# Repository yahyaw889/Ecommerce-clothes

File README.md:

<p align="center"></p>

<p align="center">

</p>

## About Laravel

Laravel is a web application framework with expressive, elegant syntax. We believe development must be an enjoyable and creative experience to be truly fulfilling. Laravel takes the pain out of development by easing common tasks used in many web projects, such as:

- [Simple, fast routing engine](https://laravel.com/docs/routing).
- [Powerful dependency injection container](https://laravel.com/docs/container).
- Multiple back-ends for [session](https://laravel.com/docs/session) and [cache](https://laravel.com/docs/cache) storage.
- Expressive, intuitive [database ORM](https://laravel.com/docs/eloquent).
- Database agnostic [schema migrations](https://laravel.com/docs/migrations).
- [Robust background job processing](https://laravel.com/docs/queues).
- [Real-time event broadcasting](https://laravel.com/docs/broadcasting).

Laravel is accessible, powerful, and provides tools required for large, robust applications.

## Learning Laravel

Laravel has the most extensive and thorough [documentation](https://laravel.com/docs) and video tutorial library of all modern web application frameworks, making it a breeze to get started with the framework.

You may also try the [Laravel Bootcamp](https://bootcamp.laravel.com), where you will be guided through building a modern Laravel application from scratch.

If you don't feel like reading, [Laracasts](https://laracasts.com) can help. Laracasts contains thousands of video tutorials on a range of topics including Laravel, modern PHP, unit testing, and JavaScript. Boost your skills by digging into our comprehensive video library.

## Laravel Sponsors

We would like to extend our thanks to the following sponsors for funding Laravel development. If you are interested in becoming a sponsor, please visit the [Laravel Partners program](https://partners.laravel.com).

### Premium Partners

- **[Vehikl](https://vehikl.com/)**
- **[Tighten Co.](https://tighten.co)**
- **[WebReinvent](https://webreinvent.com/)**
- **[Kirschbaum Development Group](https://kirschbaumdevelopment.com)**
- **[64 Robots](https://64robots.com)**
- **[Curotec](https://www.curotec.com/services/technologies/laravel/)**
- **[Cyber-Duck](https://cyber-duck.co.uk)**
- **[DevSquad](https://devsquad.com/hire-laravel-developers)**
- **[Jump24](https://jump24.co.uk)**
- **[Redberry](https://redberry.international/laravel/)**
- **[Active Logic](https://activelogic.com)**
- **[byte5](https://byte5.de)**
- **[OP.GG](https://op.gg)**

## Contributing

Thank you for considering contributing to the Laravel framework! The contribution guide can be found in the [Laravel documentation](https://laravel.com/docs/contributions).

## Code of Conduct

In order to ensure that the Laravel community is welcoming to all, please review and abide by the [Code of Conduct](https://laravel.com/docs/contributions#code-of-conduct).

## Security Vulnerabilities

If you discover a security vulnerability within Laravel, please send an e-mail to Taylor Otwell via [taylor@laravel.com](mailto:taylor@laravel.com). All security vulnerabilities will be promptly addressed.

## License

The Laravel framework is open-sourced software licensed under the [MIT license](https://opensource.org/licenses/MIT).
# E-ecommerce
# E-ecommerce

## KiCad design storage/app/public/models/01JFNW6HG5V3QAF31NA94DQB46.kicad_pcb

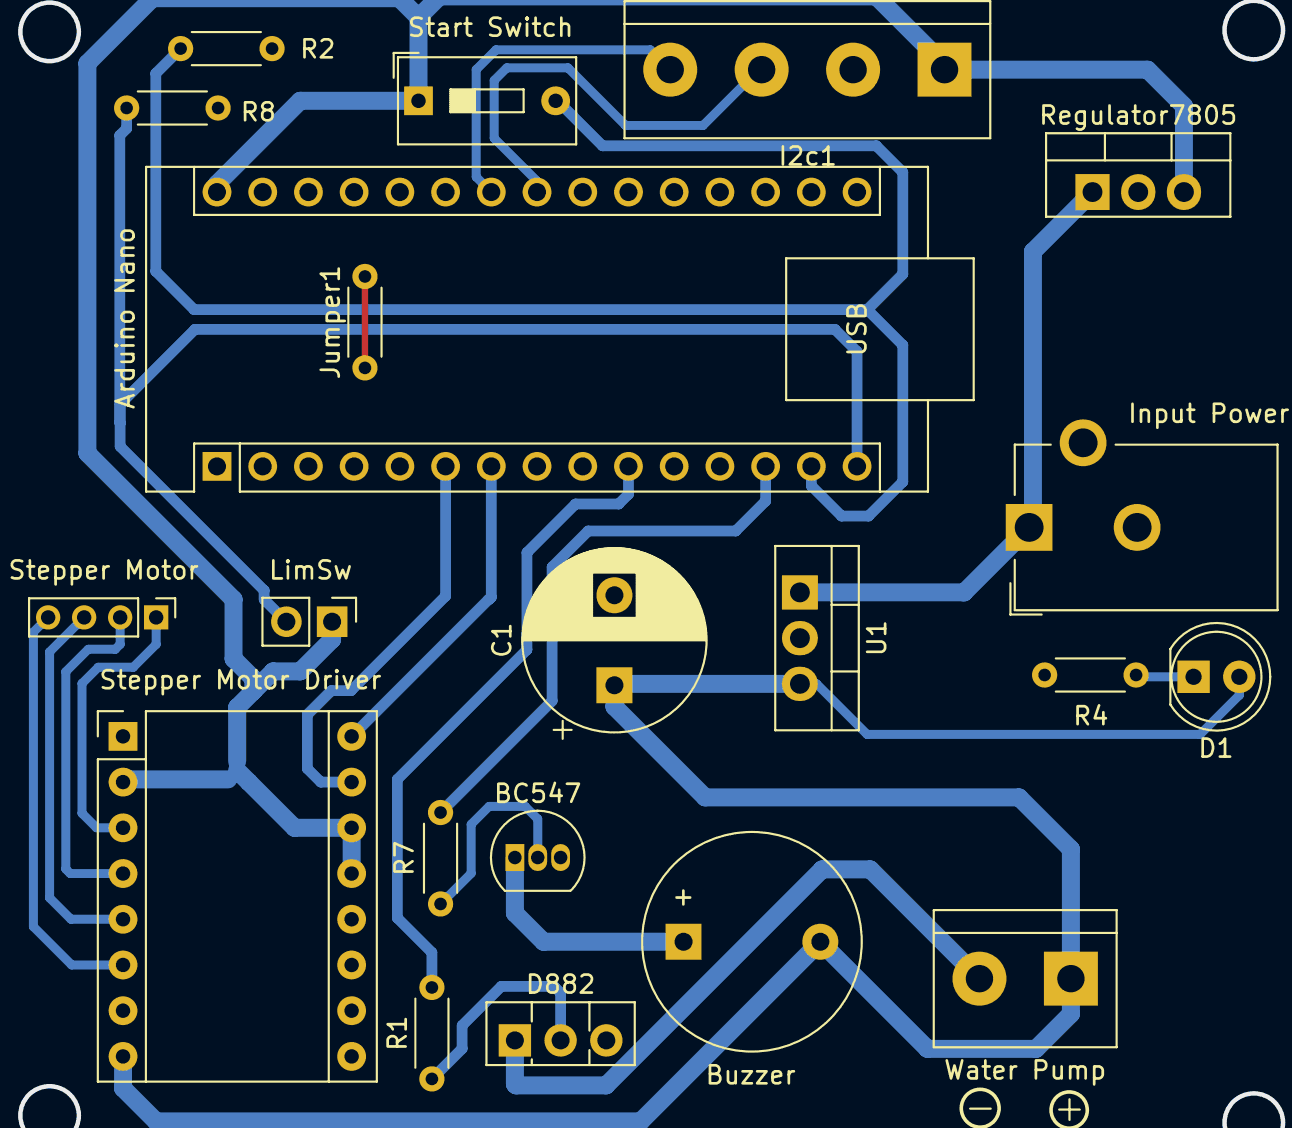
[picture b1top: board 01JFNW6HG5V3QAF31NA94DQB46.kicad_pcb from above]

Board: 2 copper layers, 21 parts (0 on the bottom side), 21 nets.

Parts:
Arduino Nano: Arduino_Nano_Every; Arduino_Nano
BC547: BC547; TO-92_Inline
Buzzer: Buzzer; Buzzer_12x9.5RM7.6
C1: 100u; CP_Radial_D10.0mm_P5.00mm
D1: LED; LED_D5.0mm
D882: BC547; TO-126-3_Vertical
I2c1: Screw_Terminal_01x04; TerminalBlock_bornier-4_P5.08mm
Input Power: Barrel_Jack_Switch; BarrelJack_CUI_PJ-102AH_Horizontal
Jumper1: R; R_Axial_DIN0204_L3.6mm_D1.6mm_P5.08mm_Horizontal
LimSw: Screw_Terminal_01x02; PinHeader_1x02_P2.54mm_Vertical
R1, R4, R7: 1k; R_Axial_DIN0204_L3.6mm_D1.6mm_P5.08mm_Horizontal
R2, R8: 10k; R_Axial_DIN0204_L3.6mm_D1.6mm_P5.08mm_Horizontal
Regulator7805: LM7805_TO220; TO-220-3_Vertical
Start Switch: SW_DPST_x2; SW_DIP_SPSTx01_Slide_9.78x4.72mm_W7.62mm_P2.54mm
Stepper Motor: Screw_Terminal_01x04; PinHeader_1x04_P2.00mm_Vertical
Stepper Motor Driver: Pololu_Breakout_A4988; Pololu_Breakout-16_15.2x20.3mm
U1: LM7812_TO220; TO-220-3_Vertical
Water Pump: Screw_Terminal_01x02; TerminalBlock_bornier-2_P5.08mm

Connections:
+5V: Arduino Nano.30 (VIN), I2c1.1, LimSw.1, Regulator7805.3 (VO), Start Switch.1 (A), Stepper Motor Driver.2 (VDD), Stepper Motor Driver.13 (~RESET), Stepper Motor Driver.14 (~SLEEP)
+12V: Buzzer.2 (+), C1.1, D1.2 (A), Stepper Motor Driver.8 (VMOT), U1.3 (VO), Water Pump.1
D3: Arduino Nano.6 (D3), Stepper Motor Driver.15 (STEP)
D4: Arduino Nano.7 (D4), Stepper Motor Driver.16 (DIR)
D8: Arduino Nano.10 (D7), R1.2
D10: Arduino Nano.13 (D10), R7.1
GND: Arduino Nano.4 (GND), Arduino Nano.29 (GND), BC547.3 (E), C1.2, D882.3 (E), I2c1.2, Input Power.2, Jumper1.1, Jumper1.2, R2.2, R4.1, R8.2, Regulator7805.2 (GND), Stepper Motor Driver.1 (GND), Stepper Motor Driver.7 (GND), U1.2 (GND)
unnamed: BC547.2 (B), R7.2
unnamed: BC547.1 (C), Buzzer.1 (-)
unnamed: D1.1 (K), R4.2
unnamed: D882.2 (B), R1.1
unnamed: D882.1 (C), Water Pump.2
unnamed: Arduino Nano.15 (MISO), LimSw.2, R8.1
unnamed: Arduino Nano.14 (MOSI), R2.1, Start Switch.2 (B)
unnamed: Stepper Motor.1, Stepper Motor Driver.3 (1B)
unnamed: Stepper Motor.2, Stepper Motor Driver.4 (1A)
unnamed: Stepper Motor.3, Stepper Motor Driver.5 (2A)
unnamed: Stepper Motor.4, Stepper Motor Driver.6 (2B)
SCL: Arduino Nano.24 (SCL/A5), I2c1.4
SDA: Arduino Nano.23 (SDA/A4), I2c1.3
Vin: Input Power.1, Regulator7805.1 (VI), U1.1 (VI)

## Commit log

2024-12-15 update on image show image
2024-12-15 Model add in the actions delete and view
2024-12-15 update on status catagery and brand isset acctive or Not acctive
2024-12-15 final project
2024-12-16 final ebrahim
2024-12-19 final v1
2024-12-21 v1.1
2024-12-21 small edit
2024-12-22 update notifaction
2025-01-02 add user api
2025-01-03 update models image to full path
2025-01-07 edit views
2025-01-09 edit socail image
2025-01-12 close limit of images in products
2025-01-14 enable delete image file
2025-01-14 add city
2025-01-15 edit city in order
2025-01-15 commit limition in order
2025-01-15 edit order error
2025-01-15 accept image webp
2025-01-28 add front end
2025-02-23 update images
2025-02-23 ads image edit
2025-04-03 add url in cors
2025-04-03 test cors
2025-04-03 test2
2025-04-05 change the cors in credentials to false
2025-04-30 cors edit to make it public
2025-05-06 edit config cors again
2025-06-27 add cart to products by session
2025-06-27 correct small issue in bootstarp/app
2025-06-28 correct cors poilcy in file htaccess
